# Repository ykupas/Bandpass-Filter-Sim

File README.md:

# Bandpass-Filter-Sim

Bandpass filter project and simulation using KiCAD (v9.0.9), FreeCAD (v1.1.1) and EMerge Software (v2.7.3) to get S parameters from a PCb design.

## 5th Bandpass Filter

The filter was designed from Marki Microwave, in this [link](https://markimicrowave.com/technical-resources/tools/lc-filter-design-tool/). It is a 5th order Chebyshev bandpass with lower cutoff frequency of 90MHz, and upper cutoff frequency of 110MHz. Passband ripple of 0.1dB, capacitors and inductors tolerance of 5% and commercial values.

The design can be viewed in SCH from KiCAD, with the results from Marki Microwave and KiCAD simulation.

## Simulation in EMerge

With the KiCAD design done, the next step was to model in FreeCAD and simulate in EMerge with the help of the macro FreeCAD-OpenEMS-Export. After modeling, meshing it and simulating, the results are shown below.

Some points are not the same because of RAM limitations in my machine, I was using only 50 points to calculate it. But it shown a good result for a simple model.

## Future works

This simulation demonstrate an example of modeling lumped components in FreeCAD for EMerge software this. Merging this feature with PCB Antenna desing, full RF systems can be simulate using open source software, as matching networks and some crazy antenna designs! Thanks for spending time here with me.

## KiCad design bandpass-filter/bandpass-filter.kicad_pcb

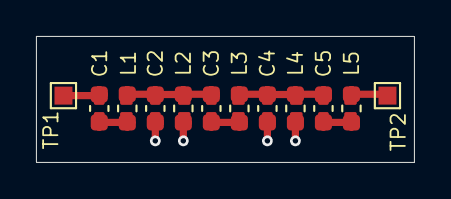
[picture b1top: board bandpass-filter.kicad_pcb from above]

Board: 2 copper layers, 21.0 x 7.0 mm, 12 parts (0 on the bottom side), 8 nets.

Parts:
C1, C5: 5.6p; C_0603_1608Metric_femSolver
C2, C4: 220p; C_0603_1608Metric_femSolver
C3: 3.3p; C_0603_1608Metric_femSolver
L1, L5: 470n; L_0603_1608Metric_femSolver
L2, L4: 12n; L_0603_1608Metric_femSolver
L3: 820n; L_0603_1608Metric_femSolver
TP1: in; TestPoint_Pad_1.0x1.0mm
TP2: out; TestPoint_Pad_1.0x1.0mm

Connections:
0: C2.2, C4.2, L2.2, L4.2
/in: C1.1, TP1.1
/out: L5.2, TP2.1
unnamed: C1.2, L1.1
unnamed: C2.1, C3.1, L1.2, L2.1
unnamed: C3.2, L3.1
unnamed: C4.1, C5.1, L3.2, L4.1
unnamed: C5.2, L5.1

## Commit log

2026-06-14 Creating SCH and circuit images.
2026-06-14 Schematic and Spice simulation complete, missing layout and EMerge simulation.
2026-06-14 Layout done, ready to export to FreeCAD.
2026-06-15 Adding FreeCAD file.
2026-06-15 Changing PCB layout.
2026-06-15 Adding FreeCAD temporary file to gitignore.
2026-06-15 Adding model to FreeCAD and creating config file for simulation.
2026-06-19 Changing PCB model to top, bot, via, PCB, lumped, ports and air.
2026-06-19 Generate python scrip using EMerge 2.7.
2026-06-19 It does not have enough memory for this mesh!
2026-06-20 CHanging top layer model for compacting mesh.
2026-06-20 Generating new script.
2026-06-20 Deleting S11 script.
2026-06-20 Adding S21 results.
2026-06-20 Adding description to README.
2026-06-20 Fixing link and file description.
2026-06-20 Finish readme script.
2026-06-20 Adding software versions.
